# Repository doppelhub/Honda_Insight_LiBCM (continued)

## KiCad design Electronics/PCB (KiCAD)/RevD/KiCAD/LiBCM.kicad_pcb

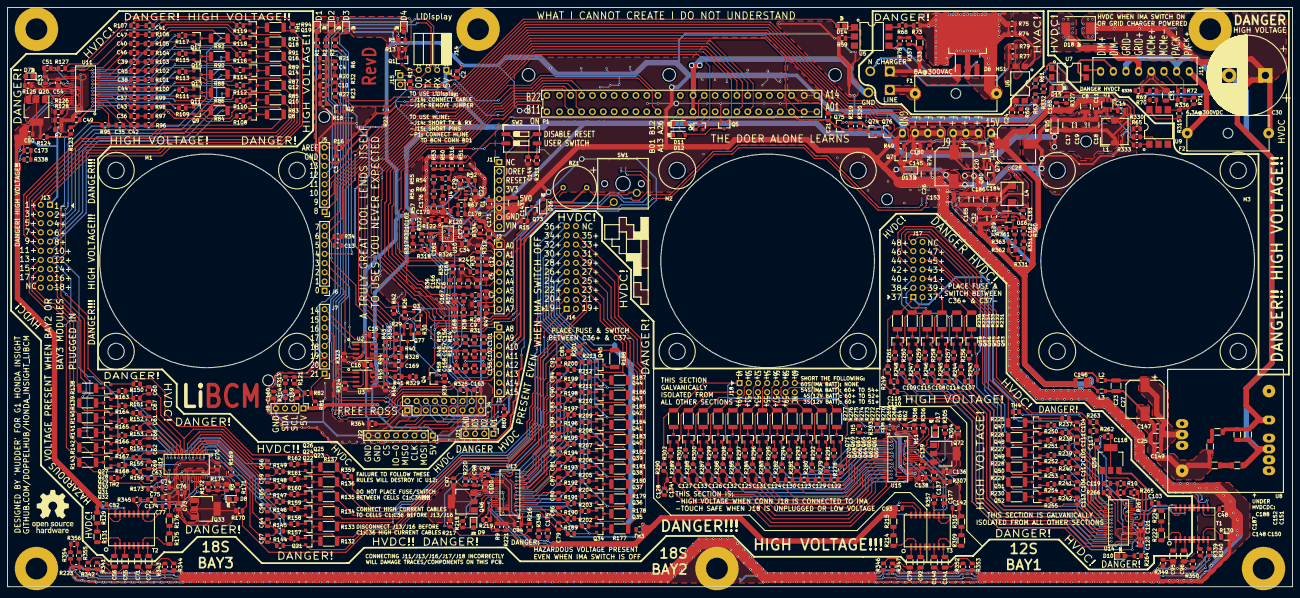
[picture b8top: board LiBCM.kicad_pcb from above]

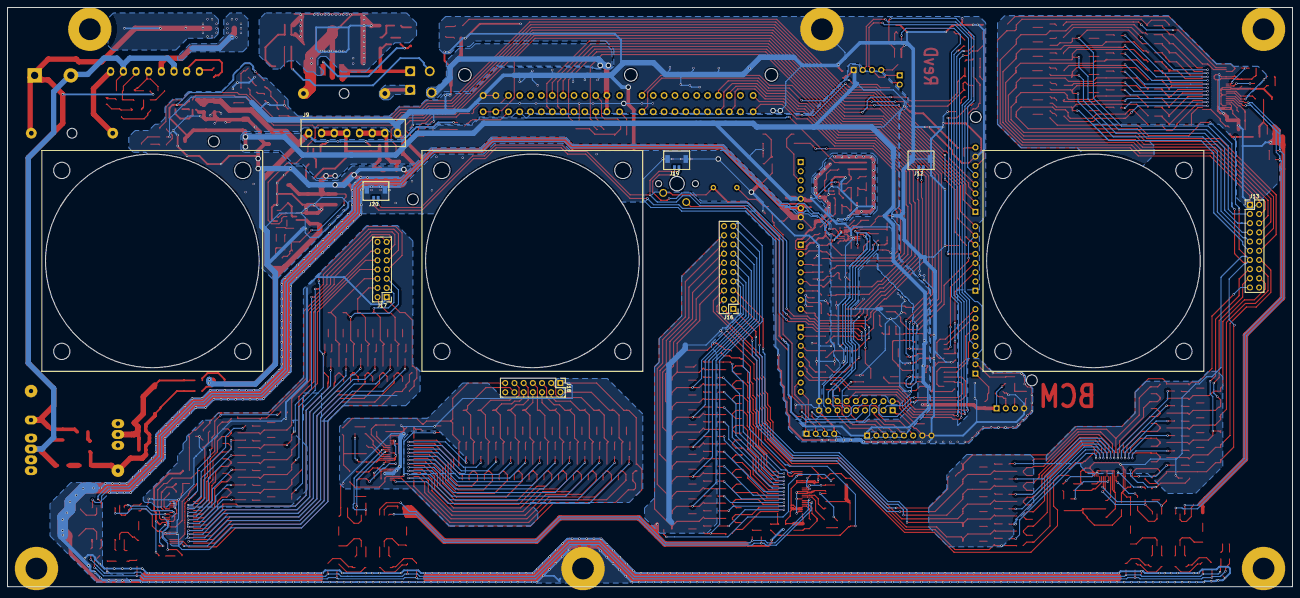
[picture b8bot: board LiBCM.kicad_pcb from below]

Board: 4 copper layers, 355.0 x 160.0 mm, 716 parts (8 on the bottom side), 583 nets.

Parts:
BZ1: Buzzer; BUZZER_WT-1205
C1, C2, C5, C6, C7, C9, C12, C13, C21, C24, C51, C53, C54, C74, C75, C76, C98, C99, C100, C101, C102, C119, C120, C121, C137, C138, C139, C144, C145, C147, C155, C156, C157, C158, C164, C166, C167, C168, C179, C180: 1u; C_0805_2012Metric
C3, C4, C10, C15, C16, C22, C29, C34, C35, C36, C37, C38, C39, C40, C41, C42, C43, C44, C45, C46, C47, C49, C50, C57, C58, C59, C60, C61, C62, C63, C64, C65, C66, C67, C68, C69, C70, C73, C79, C80, C81, C82, C83, C84, C85, C86, C87, C88, C89, C90, C91, C94, C97, C104, C105, C106, C107, C108, C109, C110, C111, C112, C113, C114, C115, C116, C117, C118, C122, C123, C124, C125, C126, C127, C128, C129, C130, C131, C132, C133, C134, C135, C136, C149, C165, C169, C176, C178, C181, C182: 100n; C_0805_2012Metric
C8, C18, C19, C143: DNP; C_1210_3225Metric
C11, C14, C170, C173, C174, C175, C177: DNP; C_0805_2012Metric
C17, C23, C25, C26, C32, C146, C153, C184, C185, C186: 22u; C_1210_3225Metric
C20, C27, C28: 220u; CP_Elec_10x10
C30: 33u; CP_Radial_D22.0mm_P10.00mm_SnapIn
C31, C151: 68n; C_1206_3216Metric
C33, C55, C56, C71, C72, C78, C92, C95, C96, C140, C141, C148, C150, C152, C187, C188: 22n; C_1206_3216Metric
C48, C52, C77, C93, C103, C142, C159, C160, C161, C162, C163, C171, C172: 100p; C_0805_2012Metric
D1, D2, D3, D4, D7, D8, D9, D10, D14, D15, D17: LED; LED_0805_2012Metric_Castellated
D5: D_Zener_ALT; D_SOD-123
D6: Q_TRIAC_A1A2G; TO-263-3_TabPin2
D11, D12, D13, D16: 1N4148W; D_SOD-123
D18: D; D_SMC
F1, F2: Fuse; Fuseholder_Cylinder-5x20mm_Schurter_0031_8201_Horizontal_Op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
H1, H2, H4, H5, H6, H7: MountingHole_Pad; MountingHole_6mm_Pad
H9: MountingHole; MountingHole_3mm
HS1: Heatsink_Pad; Heatsin-DV-T263-301E-TR
J1, J2, J3, J5, J6, J7: Conn_01x08; PinHeader_1x08_P2.54mm_Vertical
J4: Conn_02x09_Odd_Even; PinHeader_2x09_P2.54mm_Vertical
J8, J21: Conn_01x04; PinHeader_1x04_P2.54mm_Vertical
J9, J11: Screw_Terminal_01x08; CONN_1751303
J10: Screw_Terminal_01x01; SolderWire-1sqmm_1x01_D1.4mm_OD2.7mm
J12, J19, J20: Conn_02x02; CONN_WM26831CT-ND​
J13, J16: Conn_01x20; PinHeader_2x10_P2.54mm_Vertical
J14: Conn_01x04; PinSocket_1x04_P2.54mm_Horizontal
J15: Conn_01x02; PinHeader_1x02_P2.54mm_Vertical
J17, J18: Conn_01x14; PinHeader_2x07_P2.54mm_Vertical
J22: Conn_01x08; PinSocket_1x08_P2.54mm_Vertical
L1: DNP(4.7u); L_TDK_SLF7045
L2, L3: 1u; L_0805_2012Metric
L4: 15u; Inductor_CLF6045NI
M1, M2, M3: Fan; FAN_60x60OD_50x50Holes
P1: OEM_BCM_Connector; CONN_BCM_174917-6
P2: Conn_WallPlug_Earth; SolderWire-1sqmm_1x03_P5.4mm_D1.4mm_OD2.7mm
Q1, Q2, Q3, Q4, Q5, Q6, Q7, Q73, Q74, Q76, Q78, Q79, Q80: Q_NMOS_GSD; SOT-23
Q8, Q9, Q10, Q11, Q12, Q13, Q14, Q15, Q16, Q17, Q18, Q19, Q21, Q22, Q23, Q24, Q25, Q26, Q27, Q28, Q29, Q30, Q31, Q32, Q34, Q35, Q36, Q37, Q38, Q39, Q40, Q41, Q42, Q43, Q44, Q45, Q47, Q48, Q49, Q50, Q51, Q52, Q53, Q54, Q55, Q56, Q57, Q58, Q60, Q61, Q62, Q63, Q64, Q65, Q66, Q67, Q68, Q69, Q70, Q71, Q75, Q77: Q_PMOS_GSD; SOT-23
Q20, Q33, Q46, Q59, Q72: Q_NPN_BCEC; SOT-223
R1, R2, R3, R4, R5, R12, R14, R24, R25, R28, R31, R43, R44, R45, R46, R60, R81, R108, R109, R110, R111, R112, R113, R114, R115, R116, R117, R118, R119, R121, R122, R128, R157, R158, R159, R160, R161, R162, R163, R164, R165, R166, R167, R168, R174, R202, R203, R204, R205, R206, R207, R208, R209, R210, R211, R212, R213, R221, R250, R251, R252, R253, R254, R255, R256, R257, R258, R259, R260, R261, R267, R291, R292, R293, R294, R295, R296, R297, R298, R299, R300, R301, R302, R308, R326, R351, R360: 1k24; R_0805_2012Metric
R6, R20, R21, R66, R80, R323, R324: 71k5; R_0805_2012Metric
R7, R8, R9, R10, R11, R40, R41, R328, R329, R338, R345, R348, R357, R358, R364: DNP; R_0805_2012Metric
R13, R18, R19, R34, R35, R36, R37, R38, R48, R49, R51, R52, R55, R56, R58, R61, R69, R70, R71, R72, R127, R173, R220, R266, R307, R312, R315, R320, R335, R336, R361, R363: 10k; R_0805_2012Metric
R15, R26, R39, R42, R47, R57, R125, R171, R218, R264, R305, R317, R318, R319: 7k32; R_0805_2012Metric
R16, R17, R23, R50, R54, R59, R63, R65, R68, R73, R78, R82, R95, R96, R97, R98, R99, R100, R101, R102, R103, R104, R105, R106, R107, R123, R124, R144, R145, R146, R147, R148, R149, R150, R151, R152, R153, R154, R155, R156, R169, R170, R189, R190, R191, R192, R193, R194, R195, R196, R197, R198, R199, R200, R201, R216, R217, R223, R237, R238, R239, R240, R241, R242, R243, R244, R245, R246, R247, R248, R249, R262, R263, R278, R279, R280, R281, R282, R283, R284, R285, R286, R287, R288, R289, R290, R303, R304, R311, R313, R321, R322, R325, R330, R332, R333, R337, R354, R355: 100; R_0805_2012Metric
R22, R27, R32, R67, R74, R75, R77, R79, R331, R362: 100k; R_0805_2012Metric
R29, R33, R53, R120, R126, R172, R219, R265, R306, R316: 768; R_0805_2012Metric
R30, R314, R327, R334, R339, R340, R341, R342, R343, R344, R346, R347, R349, R350, R352, R353, R356, R359: 20; R_0805_2012Metric
R62, R64, R83, R84, R85, R86, R87, R88, R89, R90, R91, R92, R93, R94, R132, R133, R134, R135, R136, R137, R138, R139, R140, R141, R142, R143, R177, R178, R179, R180, R181, R182, R183, R184, R185, R186, R187, R188, R225, R226, R227, R228, R229, R230, R231, R232, R233, R234, R235, R236, R268, R269, R270, R271, R272, R273, R274, R275, R276, R277: 75; R_2010_5025Metric
R76: DNP(0); R_0805_2012Metric
R129, R130, R131, R175, R176, R214, R215, R222, R224, R309, R310: 5M; R_1206_3216Metric
SW1: SW_Push; SW_Cherry_MX_1.00u_PCB
SW2: SW_DIP_x02; SW_DIP_SPSTx02_Slide_9.78x7.26mm_W8.61mm_P2.54mm
T1, T2, T3: Trans_7490100111; Trans_7490100111A
TH1, TH2, TH3, TH4, TH5: THERMISTOR; R_0805_2012Metric
U1: AP63205WU; TSOT-23-6
U2, U3: LT1487; SOIC-8_3.9x4.9mm_P1.27mm
U4: LT1797; TSOT-23-5
U5: MOC3023M; SMDIP-6_W9.53mm
U6, U7: SFH620A-2X007T; SMDIP-4_W9.53mm_Clearance8mm
U8: EPM1510SJ; DCDC-EPM1210SJ
U9: H11D1SR2VM; SMDIP-6_W9.53mm
U10: LTC6820; LTC6820_MSOP
U11, U12, U13, U14, U15: LTC6804-2
U16: AP62301; TSOT-23-6

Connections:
+5V: BZ1.1, C1.1, C2.1, C15.2, C16.2, C17.1, C18.1, C19.1, C29.1, C34.1, C143.1, C153.1, C184.1, C185.1, C186.1, D5.1, D16.1, J1.5, J8.1, J14.1, J22.1, L1.1, L4.1, Q77.2, R16.1, R19.1, R22.1, R29.1, R35.1, R36.1, R37.1, R38.1, R48.1, R50.1, R53.1, R54.2, R58.1, R61.1, R81.2, R121.2, R311.2, R316.1, R317.1, R318.1, R326.1, R331.1, R358.2, R362.1, R363.1, SW1.2, SW2.3, U1.1, U2.8, U3.8, U4.5, U10.6, U10.7, U10.8, U10.9, U10.12
+5VP: C169.1, Q77.3, R43.1, R45.1, R358.1
+15V: C8.1, C11.1, C28.1, C32.1, C146.1, C165.1, C179.1, J9.1, L2.2, Q75.2, Q78.1, Q78.2, R76.1, R319.1, U1.3, U16.3
/5VP_GATE: Q77.1, R29.2, R30.1
/5V_BOOST: C14.2, U1.6
/5V_BOOST_ALT: C181.2, U16.6
/5V_COMP: C182.2, R363.2
/5V_ENABLE: C10.2, R22.2, R23.1, R27.1, R32.1, R327.2, U1.2, U16.5
/5V_EN_FET: Q2.3, R23.2
/5V_EN_PULSE: C165.2, R327.1
/5V_FB_ALT: C182.1, R360.2, R361.1, U16.4
/5V_SW: C14.1, L1.2, U1.5
/5V_SW_ALT: C181.1, L4.2, U16.2
/12NEG_RAW: C23.2, C25.2, C27.2, C147.2, C148.2, C149.1, C187.2, L3.2, U8.7
/12POS_RAW: C23.1, C25.1, C27.1, C147.1, C149.2, L2.1, U8.5
/12V_ALWAYS: D11.1, D12.1, P1.A13
/12V_KEYON: P1.A01, P1.A02, R6.2, R32.2
/38(HW_VER1): J4.2, R364.2
/52k5_L1: R331.2, R351.1, R362.2
/52k5_L2: R351.2, R360.1
/+12V_FAN: C20.1, C26.1, C145.1, C180.1, D13.1, J9.2, J9.3, J9.4, Q80.3, R76.2
/AREF: C3.1, J5.8, R16.2
/BATTFANH: D12.2, P1.A24, Q5.3
/BATTFANH_EN: J3.1, Q5.1, R42.1
/BATTFANL: D11.2, P1.A11, Q6.3
/BATTFANL_EN: J2.8, Q6.1, R47.1
/BATTSCI1: P1.A20, R46.1, R329.2, U3.6
/BATTSCI2: P1.A07, R41.1, R45.2, U3.7
/BATTSCI_DE: J4.3, R324.1, U3.3
/BATTSCI_REn: J4.4, U3.2
/BATTSCI_RX: J7.5, U3.1
/BATTSCI_TX: J7.6, U3.4
/BATT_CURRENT_ADC: C171.1, J2.1, R334.2
/BATT_CURRENT_I2V: C22.1, R51.1, R52.2, U4.3
/BAT_T: R41.2, R329.1
/BUZ1: BZ1.2, D16.2, Q73.3
/BUZZER: J4.7, Q73.1, R15.1
/COVER_SWITCH: J4.6, R80.1, SW1.1
/FAN-: C145.2, C180.2, D13.2, J9.5, J9.6, J9.7, Q7.3
/FAN_PWM: J5.4, Q7.1, R49.1
/GPIO-0: J4.5, J22.5
/GPIO-1: J3.7, J21.1
/GPIO-2: J3.8, J21.2
/GPIO-3: J4.8, J21.3
/GRID_EN: D14.2, J5.3
/GRID_EN_LED_A: D14.1, U5.1
/GRID_EN_LED_C: R59.2, U5.2
/GRID_HVDC+: D18.2, J11.4
/GRID_PWM: D15.2, J5.1
/GRID_PWM+: J11.1, U7.4
/GRID_PWM-: J11.2, U7.3
/GRID_PWM_DIV: R63.1, R332.1
/GRID_PWM_LED_A: D15.1, U7.1
/GRID_PWM_LED_C: R332.2, U7.2
/GRID_SENSE: C24.1, J5.2, R60.2
/GRID_SENSE_L1: R74.2, R75.2, U6.1
/GRID_SENSE_L2: R77.2, R79.2, U6.2
/GRID_SENSE_NOISY: R60.1, R61.2, U6.4
/HLINE: J15.2, R17.2
/HLINE_CONN: P1.B01, R17.1
/HMI_EN: J5.5, Q1.1, R13.1
/HMI_EN_OD: J14.4, Q1.3
/HMI_RX: J7.3, J14.2
/HMI_TX: J7.4, J14.3, J15.1
/HVDC_POS_UNFUSED: F2.1, J11.8
/IGNITION_SENSE: C4.1, J5.6, R20.1, R21.2
/I_SENSOR_NEG: C21.2, P1.A16, Q76.3
/I_SENSOR_POS: C21.1, P1.A03, Q75.3
/I_SENSOR_RAW: P1.A04, R50.2, R51.2, R53.2, R316.2
/KEYON_DIV: R6.1, R21.1
/L1: D6.2, F1.1, HS1.1, R73.1, R74.1, R75.1
/L1_GRID: C33.1, D6.1, J10.1, R337.1
/L1_SNUB: R78.1, R337.2
/L1_UNFUSED: F1.2, P2.1
/L2: P2.2, R77.1, R79.1
/LED1: J3.5, R1.2
/LED1R: D1.2, R1.1
/LED2: J3.6, R2.2
/LED2R: D2.2, R2.1
/LED3: J4.10, R3.2
/LED3R: D3.2, R3.1
/LED4: J4.12, R5.2
/LED4R: D4.2, R5.1
/LOAD5V_FET: Q3.3, R30.2
/LiBCM BMS/BIAS_A: R129.1, R131.2
/LiBCM BMS/BIAS_B: R175.2, R176.1
/LiBCM BMS/BIAS_C: R214.2, R215.1
/LiBCM BMS/BIAS_D: R222.2, R224.1
/LiBCM BMS/BIAS_E: R309.2, R310.1
/LiBCM BMS/C0_A: C41.2, C47.2, R107.1, U11.26
/LiBCM BMS/C0_B: C63.2, C69.2, R156.1, U12.26
/LiBCM BMS/C0_C: C85.2, C91.2, R201.1, U13.26
/LiBCM BMS/C0_D: C110.2, C116.2, R249.1, U14.26
/LiBCM BMS/C0_E: C128.2, C134.2, R290.1, U15.26
/LiBCM BMS/C1_A: C40.2, C47.1, R106.1, U11.24
/LiBCM BMS/C1_B: C62.2, C69.1, R155.1, U12.24
/LiBCM BMS/C1_C: C84.2, C91.1, R200.1, U13.24
/LiBCM BMS/C1_D: C109.2, C116.1, R248.1, U14.24
/LiBCM BMS/C1_E: C127.2, C134.1, R289.1, U15.24
/LiBCM BMS/C2_A: C40.1, C46.2, R105.1, U11.22
/LiBCM BMS/C2_B: C62.1, C68.2, R154.1, U12.22
/LiBCM BMS/C2_C: C84.1, C90.2, R199.1, U13.22
/LiBCM BMS/C2_D: C109.1, C115.2, R247.1, U14.22
/LiBCM BMS/C2_E: C127.1, C133.2, R288.1, U15.22
/LiBCM BMS/C3_A: C39.2, C46.1, R104.1, U11.20
/LiBCM BMS/C3_B: C61.2, C68.1, R153.1, U12.20
/LiBCM BMS/C3_C: C83.2, C90.1, R198.1, U13.20
/LiBCM BMS/C3_D: C108.2, C115.1, R246.1, U14.20
/LiBCM BMS/C3_E: C126.2, C133.1, R287.1, U15.20
/LiBCM BMS/C4_A: C39.1, C45.2, R103.1, U11.18
/LiBCM BMS/C4_B: C61.1, C67.2, R152.1, U12.18
/LiBCM BMS/C4_C: C83.1, C89.2, R197.1, U13.18
/LiBCM BMS/C4_D: C108.1, C114.2, R245.1, U14.18
/LiBCM BMS/C4_E: C126.1, C132.2, R286.1, U15.18
/LiBCM BMS/C5_A: C38.2, C45.1, R102.1, U11.16
/LiBCM BMS/C5_B: C60.2, C67.1, R151.1, U12.16
/LiBCM BMS/C5_C: C82.2, C89.1, R196.1, U13.16
/LiBCM BMS/C5_D: C107.2, C114.1, R244.1, U14.16
/LiBCM BMS/C5_E: C125.2, C132.1, R285.1, U15.16
/LiBCM BMS/C6_A: C38.1, C44.2, R101.1, U11.14
/LiBCM BMS/C6_B: C60.1, C66.2, R150.1, U12.14
/LiBCM BMS/C6_C: C82.1, C88.2, R195.1, U13.14
/LiBCM BMS/C6_D: C107.1, C113.2, R243.1, U14.14
/LiBCM BMS/C6_E: C125.1, C131.2, R284.1, U15.14
/LiBCM BMS/C7_A: C37.2, C44.1, R100.1, U11.12
/LiBCM BMS/C7_B: C59.2, C66.1, R149.1, U12.12
/LiBCM BMS/C7_C: C81.2, C88.1, R194.1, U13.12
/LiBCM BMS/C7_D: C106.2, C113.1, R242.1, U14.12
/LiBCM BMS/C7_E: C124.2, C131.1, R283.1, U15.12
/LiBCM BMS/C8_A: C37.1, C43.2, R99.1, U11.10
/LiBCM BMS/C8_B: C59.1, C65.2, R148.1, U12.10
/LiBCM BMS/C8_C: C81.1, C87.2, R193.1, U13.10
/LiBCM BMS/C8_D: C106.1, C112.2, R241.1, U14.10
/LiBCM BMS/C8_E: C124.1, C130.2, R282.1, U15.10
/LiBCM BMS/C9_A: C36.2, C43.1, R98.1, U11.8
/LiBCM BMS/C9_B: C58.2, C65.1, R147.1, U12.8
/LiBCM BMS/C9_C: C80.2, C87.1, R192.1, U13.8
/LiBCM BMS/C9_D: C105.2, C112.1, R240.1, U14.8
/LiBCM BMS/C9_E: C123.2, C130.1, R281.1, U15.8
/LiBCM BMS/C10_A: C36.1, C42.2, R97.1, U11.6
/LiBCM BMS/C10_B: C58.1, C64.2, R146.1, U12.6
/LiBCM BMS/C10_C: C80.1, C86.2, R191.1, U13.6
/LiBCM BMS/C10_D: C105.1, C111.2, R239.1, U14.6
/LiBCM BMS/C10_E: C123.1, C129.2, R280.1, U15.6
/LiBCM BMS/C10pos: J13.11, Q10.2, R84.2, R97.2
/LiBCM BMS/C11_A: C35.2, C42.1, R96.1, U11.4
/LiBCM BMS/C11_B: C57.2, C64.1, R145.1, U12.4
/LiBCM BMS/C11_C: C79.2, C86.1, R190.1, U13.4
/LiBCM BMS/C11_D: C104.2, C111.1, R238.1, U14.4
/LiBCM BMS/C11_E: C122.2, C129.1, R279.1, U15.4
/LiBCM BMS/C11pos: J13.12, Q9.2, R83.2, R96.2
/LiBCM BMS/C12_A: C35.1, R95.1, U11.2
/LiBCM BMS/C12_B: C57.1, R144.1, U12.2
/LiBCM BMS/C12_C: C79.1, R189.1, U13.2
/LiBCM BMS/C12_D: C104.1, R237.1, U14.2
/LiBCM BMS/C12_E: C122.1, R278.1, U15.2
/LiBCM BMS/CELL1pos: J13.2, Q19.2, R93.2, R106.2
/LiBCM BMS/CELL2pos: J13.3, Q18.2, R92.2, R105.2
/LiBCM BMS/CELL3pos: J13.4, Q17.2, R91.2, R104.2
/LiBCM BMS/CELL4pos: J13.5, Q16.2, R90.2, R103.2
/LiBCM BMS/CELL5pos: J13.6, Q15.2, R89.2, R102.2
/LiBCM BMS/CELL6pos: J13.7, Q14.2, R88.2, R101.2
/LiBCM BMS/CELL7pos: J13.8, Q13.2, R87.2, R100.2
/LiBCM BMS/CELL8pos: J13.9, Q12.2, R86.2, R99.2
/LiBCM BMS/CELL9pos: J13.10, Q11.2, R85.2, R98.2
/LiBCM BMS/CELL13pos: J13.14, Q32.2, R142.2, R155.2
/LiBCM BMS/CELL14pos: J13.15, Q31.2, R141.2, R154.2
/LiBCM BMS/CELL15pos: J13.16, Q30.2, R140.2, R153.2
/LiBCM BMS/CELL16pos: J13.17, Q29.2, R139.2, R152.2
/LiBCM BMS/CELL17pos: J13.18, Q28.2, R138.2, R151.2
/LiBCM BMS/CELL18pos: J13.19, Q27.2, R137.2, R150.2, R359.2
/LiBCM BMS/CELL19neg: J16.1, R359.1
/LiBCM BMS/CELL19pos: J16.2, Q26.2, R136.2, R149.2
/LiBCM BMS/CELL20pos: J16.3, Q25.2, R135.2, R148.2
/LiBCM BMS/CELL21pos: J16.4, Q24.2, R134.2, R147.2
/LiBCM BMS/CELL22pos: J16.5, Q23.2, R133.2, R146.2
/LiBCM BMS/CELL23pos: J16.6, Q22.2, R132.2, R145.2
/LiBCM BMS/CELL25pos: J16.8, Q45.2, R187.2, R200.2
/LiBCM BMS/CELL26pos: J16.9, Q44.2, R186.2, R199.2
/LiBCM BMS/CELL27pos: J16.10, Q43.2, R185.2, R198.2
/LiBCM BMS/CELL28pos: J16.11, Q42.2, R184.2, R197.2
/LiBCM BMS/CELL29pos: J16.12, Q41.2, R183.2, R196.2
/LiBCM BMS/CELL30pos: J16.13, Q40.2, R182.2, R195.2
/LiBCM BMS/CELL31pos: J16.14, Q39.2, R181.2, R194.2
/LiBCM BMS/CELL32pos: J16.15, Q38.2, R180.2, R193.2
/LiBCM BMS/CELL33pos: J16.16, Q37.2, R179.2, R192.2
/LiBCM BMS/CELL34pos: J16.17, Q36.2, R178.2, R191.2
/LiBCM BMS/CELL35pos: J16.18, Q35.2, R177.2, R190.2
/LiBCM BMS/CELL36pos: J16.19, Q34.2, R189.2, R216.1, R217.2
/LiBCM BMS/CELL37pos: J17.2, Q58.2, R235.2, R248.2
/LiBCM BMS/CELL38pos: J17.3, Q57.2, R234.2, R247.2
/LiBCM BMS/CELL39pos: J17.4, Q56.2, R233.2, R246.2
/LiBCM BMS/CELL40pos: J17.5, Q55.2, R232.2, R245.2
/LiBCM BMS/CELL41pos: J17.6, Q54.2, R231.2, R244.2
/LiBCM BMS/CELL42pos: J17.7, Q53.2, R230.2, R243.2
/LiBCM BMS/CELL43pos: J17.8, Q52.2, R229.2, R242.2
/LiBCM BMS/CELL44pos: J17.9, Q51.2, R228.2, R241.2
/LiBCM BMS/CELL45pos: J17.10, Q50.2, R227.2, R240.2
/LiBCM BMS/CELL46pos: J17.11, Q49.2, R226.2, R239.2
/LiBCM BMS/CELL47pos: J17.12, Q48.2, R225.2, R238.2
/LiBCM BMS/CELL48pos: J17.13, Q47.2, R237.2, R262.1, R263.2
/LiBCM BMS/CELL49pos: J18.2, Q71.2, R276.2, R289.2
/LiBCM BMS/CELL50pos: J18.3, Q70.2, R275.2, R288.2
/LiBCM BMS/CELL51pos: J18.4, Q69.2, R274.2, R287.2
/LiBCM BMS/CELL52pos: J18.5, Q68.2, R273.2, R286.2
/LiBCM BMS/CELL53pos: J18.6, Q67.2, R272.2, R285.2
/LiBCM BMS/CELL54pos: J18.7, Q66.2, R271.2, R284.2
/LiBCM BMS/CELL55pos: J18.8, Q65.2, R270.2, R283.2
/LiBCM BMS/CELL56pos: J18.9, Q64.2, R269.2, R282.2
/LiBCM BMS/CELL57pos: J18.10, Q63.2, R268.2, R281.2
/LiBCM BMS/CELL58pos: J18.11, Q62.2, R64.2, R280.2
/LiBCM BMS/CELL59pos: J18.12, Q61.2, R62.2, R279.2
/LiBCM BMS/CELL60pos: J18.13, Q60.2, R278.2, R303.1, R304.2
/LiBCM BMS/DRIVE_A: Q20.1, U11.38
/LiBCM BMS/DRIVE_B: Q33.1, U12.38
/LiBCM BMS/DRIVE_C: Q46.1, U13.38
/LiBCM BMS/DRIVE_D: Q59.1, U14.38
/LiBCM BMS/DRIVE_E: Q72.1, U15.38
/LiBCM BMS/IB_6820: R120.1, U10.16
/LiBCM BMS/IB_A: R126.1, U11.44
/LiBCM BMS/IB_B: R172.1, U12.44
/LiBCM BMS/IB_C: R219.1, U13.44
/LiBCM BMS/IB_D: R265.1, U14.44
/LiBCM BMS/IB_E: R306.1, U15.44
/LiBCM BMS/IC_6820: R120.2, R122.1, U10.15
/LiBCM BMS/IC_A: R7.2, R126.2, R128.2, U11.43
/LiBCM BMS/IC_B: R8.2, R172.2, R174.2, U12.43
/LiBCM BMS/IC_C: R9.2, R219.2, R221.2, U13.43
/LiBCM BMS/IC_D: R10.2, R265.2, R267.2, U14.43
/LiBCM BMS/IC_E: R11.2, R306.2, R308.2, U15.43
/LiBCM BMS/IMA_A: C173.1, T2.14, U11.41
/LiBCM BMS/IMA_B: C174.1, T2.9, U12.41
/LiBCM BMS/IMA_C: C175.1, T3.14, U13.41
/LiBCM BMS/IMA_D: T1.14, U14.41
/LiBCM BMS/IMA_E: C177.1, T3.9, U15.41
/LiBCM BMS/IM_6820: C172.1, T1.9, U10.10
/LiBCM BMS/IM_ISOA_X: C55.2, T2.3
/LiBCM BMS/IM_ISOB_X: C72.2, T2.8
/LiBCM BMS/IM_ISOC_X: C92.2, T3.3
/LiBCM BMS/IM_ISOD_X: C96.2, T1.3
/LiBCM BMS/IM_ISOE_X: C141.2, T3.8
/LiBCM BMS/IM_ISO_SAFETY: R340.2, T1.8
/LiBCM BMS/IM_ISO_STAR: R223.1, R340.1, R341.1, R344.1, R347.1, R350.1, R353.1, R355.1
/LiBCM BMS/IM_TERMA: C55.1, R341.2
/LiBCM BMS/IM_TERMB: C72.1, R344.2
/LiBCM BMS/IM_TERMC: C92.1, R347.2
/LiBCM BMS/IM_TERMD: C96.1, R350.2
/LiBCM BMS/IM_TERME: C141.1, R353.2
/LiBCM BMS/IM_TERM_STAR: R355.2, R356.1
/LiBCM BMS/IPA_A: R338.1, T2.16, U11.42
/LiBCM BMS/IPA_B: R345.1, T2.11, U12.42
/LiBCM BMS/IPA_C: R348.1, T3.16, U13.42
/LiBCM BMS/IPA_D: T1.16, U14.42
/LiBCM BMS/IPA_E: R357.1, T3.11, U15.42
/LiBCM BMS/IP_6820: C172.2, T1.11, U10.11
/LiBCM BMS/IP_ISOA_X: C56.2, T2.1
/LiBCM BMS/IP_ISOB_X: C71.2, T2.6
/LiBCM BMS/IP_ISOC_X: C78.2, T3.1
/LiBCM BMS/IP_ISOD_X: C95.2, T1.1
/LiBCM BMS/IP_ISOE_X: C140.2, T3.6
/LiBCM BMS/IP_ISO_SAFETY: R339.2, T1.6
/LiBCM BMS/IP_ISO_STAR: R223.2, R339.1, R342.1, R343.1, R346.1, R349.1, R352.1, R354.2
/LiBCM BMS/IP_TERMA: C56.1, R342.2
/LiBCM BMS/IP_TERMB: C71.1, R343.2
/LiBCM BMS/IP_TERMC: C78.1, R346.2
/LiBCM BMS/IP_TERMD: C95.1, R349.2
/LiBCM BMS/IP_TERME: C140.1, R352.2
/LiBCM BMS/IP_TERM_STAR: R354.1, R356.2
/LiBCM BMS/ISOA_TAP: R131.1, T2.2
/LiBCM BMS/ISOB_TAP: R175.1, T2.7
/LiBCM BMS/ISOC_TAP: R214.1, T3.2
/LiBCM BMS/ISOD_TAP: R222.1, T1.2
/LiBCM BMS/ISOE_TAP: R309.1, T3.7
/LiBCM BMS/LED_A: D7.2, R125.1
/LiBCM BMS/LED_B: D8.2, R171.1
/LiBCM BMS/LED_C: D9.2, R218.1
/LiBCM BMS/LED_D: D10.2, R264.1
/LiBCM BMS/LED_E: D17.2, R305.1
/LiBCM BMS/QC1_A: Q19.3, R94.1
/LiBCM BMS/QC1_B: Q32.3, R143.1
/LiBCM BMS/QC1_C: Q45.3, R188.1
/LiBCM BMS/QC1_D: Q58.3, R236.1
/LiBCM BMS/QC1_E: Q71.3, R277.1
/LiBCM BMS/QC2_A: Q18.3, R93.1
/LiBCM BMS/QC2_B: Q31.3, R142.1
/LiBCM BMS/QC2_C: Q44.3, R187.1
/LiBCM BMS/QC2_D: Q57.3, R235.1
/LiBCM BMS/QC2_E: Q70.3, R276.1
/LiBCM BMS/QC3_A: Q17.3, R92.1
/LiBCM BMS/QC3_B: Q30.3, R141.1
/LiBCM BMS/QC3_C: Q43.3, R186.1
/LiBCM BMS/QC3_D: Q56.3, R234.1
/LiBCM BMS/QC3_E: Q69.3, R275.1
/LiBCM BMS/QC4_A: Q16.3, R91.1
/LiBCM BMS/QC4_B: Q29.3, R140.1
/LiBCM BMS/QC4_C: Q42.3, R185.1
/LiBCM BMS/QC4_D: Q55.3, R233.1
/LiBCM BMS/QC4_E: Q68.3, R274.1
/LiBCM BMS/QC5_A: Q15.3, R90.1
/LiBCM BMS/QC5_B: Q28.3, R139.1
/LiBCM BMS/QC5_C: Q41.3, R184.1
/LiBCM BMS/QC5_D: Q54.3, R232.1
/LiBCM BMS/QC5_E: Q67.3, R273.1
/LiBCM BMS/QC6_A: Q14.3, R89.1
/LiBCM BMS/QC6_B: Q27.3, R138.1
/LiBCM BMS/QC6_C: Q40.3, R183.1
/LiBCM BMS/QC6_D: Q53.3, R231.1
/LiBCM BMS/QC6_E: Q66.3, R272.1
/LiBCM BMS/QC7_A: Q13.3, R88.1
/LiBCM BMS/QC7_B: Q26.3, R137.1
/LiBCM BMS/QC7_C: Q39.3, R182.1
/LiBCM BMS/QC7_D: Q52.3, R230.1
/LiBCM BMS/QC7_E: Q65.3, R271.1
/LiBCM BMS/QC8_A: Q12.3, R87.1
/LiBCM BMS/QC8_B: Q25.3, R136.1
/LiBCM BMS/QC8_C: Q38.3, R181.1
/LiBCM BMS/QC8_D: Q51.3, R229.1
/LiBCM BMS/QC8_E: Q64.3, R270.1
/LiBCM BMS/QC9_A: Q11.3, R86.1
/LiBCM BMS/QC9_B: Q24.3, R135.1
/LiBCM BMS/QC9_C: Q37.3, R180.1
/LiBCM BMS/QC9_D: Q50.3, R228.1
/LiBCM BMS/QC9_E: Q63.3, R269.1
/LiBCM BMS/QC10_A: Q10.3, R85.1
/LiBCM BMS/QC10_B: Q23.3, R134.1
/LiBCM BMS/QC10_C: Q36.3, R179.1
/LiBCM BMS/QC10_D: Q49.3, R227.1
/LiBCM BMS/QC10_E: Q62.3, R268.1
/LiBCM BMS/QC11_A: Q9.3, R84.1
/LiBCM BMS/QC11_B: Q22.3, R133.1
/LiBCM BMS/QC11_C: Q35.3, R178.1
/LiBCM BMS/QC11_D: Q48.3, R226.1
/LiBCM BMS/QC11_E: Q61.3, R64.1
/LiBCM BMS/QC12_A: Q8.3, R83.1
/LiBCM BMS/QC12_B: Q21.3, R132.1
/LiBCM BMS/QC12_C: Q34.3, R177.1
/LiBCM BMS/QC12_D: Q47.3, R225.1
/LiBCM BMS/QC12_E: Q60.3, R62.1
/LiBCM BMS/S1_A: R119.1, U11.25
/LiBCM BMS/S1_B: R168.1, U12.25
/LiBCM BMS/S1_C: R213.1, U13.25
/LiBCM BMS/S1_D: R261.1, U14.25
/LiBCM BMS/S1_E: R302.1, U15.25
/LiBCM BMS/S1b_A: Q19.1, R119.2
/LiBCM BMS/S1b_B: Q32.1, R168.2
/LiBCM BMS/S1b_C: Q45.1, R213.2
/LiBCM BMS/S1b_D: Q58.1, R261.2
/LiBCM BMS/S1b_E: Q71.1, R302.2
/LiBCM BMS/S2_A: R118.1, U11.23
/LiBCM BMS/S2_B: R167.1, U12.23
/LiBCM BMS/S2_C: R212.1, U13.23
/LiBCM BMS/S2_D: R260.1, U14.23
/LiBCM BMS/S2_E: R301.1, U15.23
/LiBCM BMS/S2b_A: Q18.1, R118.2
/LiBCM BMS/S2b_B: Q31.1, R167.2
/LiBCM BMS/S2b_C: Q44.1, R212.2
/LiBCM BMS/S2b_D: Q57.1, R260.2
/LiBCM BMS/S2b_E: Q70.1, R301.2
/LiBCM BMS/S3_A: R117.1, U11.21
/LiBCM BMS/S3_B: R166.1, U12.21
/LiBCM BMS/S3_C: R211.1, U13.21
/LiBCM BMS/S3_D: R259.1, U14.21
/LiBCM BMS/S3_E: R300.1, U15.21
/LiBCM BMS/S3b_A: Q17.1, R117.2
/LiBCM BMS/S3b_B: Q30.1, R166.2
/LiBCM BMS/S3b_C: Q43.1, R211.2
/LiBCM BMS/S3b_D: Q56.1, R259.2
/LiBCM BMS/S3b_E: Q69.1, R300.2
/LiBCM BMS/S4_A: R116.1, U11.19
/LiBCM BMS/S4_B: R165.1, U12.19
/LiBCM BMS/S4_C: R210.1, U13.19
/LiBCM BMS/S4_D: R258.1, U14.19
/LiBCM BMS/S4_E: R299.1, U15.19
/LiBCM BMS/S4b_A: Q16.1, R116.2
/LiBCM BMS/S4b_B: Q29.1, R165.2
/LiBCM BMS/S4b_C: Q42.1, R210.2
/LiBCM BMS/S4b_D: Q55.1, R258.2
/LiBCM BMS/S4b_E: Q68.1, R299.2
/LiBCM BMS/S5_A: R115.1, U11.17
/LiBCM BMS/S5_B: R164.1, U12.17
/LiBCM BMS/S5_C: R209.1, U13.17
/LiBCM BMS/S5_D: R257.1, U14.17
/LiBCM BMS/S5_E: R298.1, U15.17
/LiBCM BMS/S5b_A: Q15.1, R115.2
/LiBCM BMS/S5b_B: Q28.1, R164.2
/LiBCM BMS/S5b_C: Q41.1, R209.2
/LiBCM BMS/S5b_D: Q54.1, R257.2
/LiBCM BMS/S5b_E: Q67.1, R298.2
/LiBCM BMS/S6_A: R114.1, U11.15
/LiBCM BMS/S6_B: R163.1, U12.15
/LiBCM BMS/S6_C: R208.1, U13.15
/LiBCM BMS/S6_D: R256.1, U14.15
/LiBCM BMS/S6_E: R297.1, U15.15
/LiBCM BMS/S6b_A: Q14.1, R114.2
/LiBCM BMS/S6b_B: Q27.1, R163.2
/LiBCM BMS/S6b_C: Q40.1, R208.2
/LiBCM BMS/S6b_D: Q53.1, R256.2
/LiBCM BMS/S6b_E: Q66.1, R297.2
/LiBCM BMS/S7_A: R113.1, U11.13
/LiBCM BMS/S7_B: R162.1, U12.13
/LiBCM BMS/S7_C: R207.1, U13.13
/LiBCM BMS/S7_D: R255.1, U14.13
/LiBCM BMS/S7_E: R296.1, U15.13
/LiBCM BMS/S7b_A: Q13.1, R113.2
/LiBCM BMS/S7b_B: Q26.1, R162.2
/LiBCM BMS/S7b_C: Q39.1, R207.2
/LiBCM BMS/S7b_D: Q52.1, R255.2
/LiBCM BMS/S7b_E: Q65.1, R296.2
/LiBCM BMS/S8_A: R112.1, U11.11
/LiBCM BMS/S8_B: R161.1, U12.11
/LiBCM BMS/S8_C: R206.1, U13.11
/LiBCM BMS/S8_D: R254.1, U14.11
/LiBCM BMS/S8_E: R295.1, U15.11
/LiBCM BMS/S8b_A: Q12.1, R112.2
/LiBCM BMS/S8b_B: Q25.1, R161.2
/LiBCM BMS/S8b_C: Q38.1, R206.2
/LiBCM BMS/S8b_D: Q51.1, R254.2
/LiBCM BMS/S8b_E: Q64.1, R295.2
/LiBCM BMS/S9_A: R111.1, U11.9
/LiBCM BMS/S9_B: R160.1, U12.9
/LiBCM BMS/S9_C: R205.1, U13.9
/LiBCM BMS/S9_D: R253.1, U14.9
/LiBCM BMS/S9_E: R294.1, U15.9
/LiBCM BMS/S9b_A: Q11.1, R111.2
/LiBCM BMS/S9b_B: Q24.1, R160.2
/LiBCM BMS/S9b_C: Q37.1, R205.2
/LiBCM BMS/S9b_D: Q50.1, R253.2
/LiBCM BMS/S9b_E: Q63.1, R294.2
/LiBCM BMS/S10_A: R110.1, U11.7
/LiBCM BMS/S10_B: R159.1, U12.7
/LiBCM BMS/S10_C: R204.1, U13.7
/LiBCM BMS/S10_D: R252.1, U14.7
/LiBCM BMS/S10_E: R293.1, U15.7
/LiBCM BMS/S10b_A: Q10.1, R110.2
/LiBCM BMS/S10b_B: Q23.1, R159.2
/LiBCM BMS/S10b_C: Q36.1, R204.2
/LiBCM BMS/S10b_D: Q49.1, R252.2
/LiBCM BMS/S10b_E: Q62.1, R293.2
/LiBCM BMS/S11_A: R109.1, U11.5
/LiBCM BMS/S11_B: R158.1, U12.5
/LiBCM BMS/S11_C: R203.1, U13.5
/LiBCM BMS/S11_D: R251.1, U14.5
/LiBCM BMS/S11_E: R292.1, U15.5
/LiBCM BMS/S11b_A: Q9.1, R109.2
/LiBCM BMS/S11b_B: Q22.1, R158.2
/LiBCM BMS/S11b_C: Q35.1, R203.2
/LiBCM BMS/S11b_D: Q48.1, R251.2
/LiBCM BMS/S11b_E: Q61.1, R292.2
/LiBCM BMS/S12_A: R108.1, U11.3
/LiBCM BMS/S12_B: R157.1, U12.3
/LiBCM BMS/S12_C: R202.1, U13.3
/LiBCM BMS/S12_D: R250.1, U14.3
/LiBCM BMS/S12_E: R291.1, U15.3
/LiBCM BMS/S12b_A: Q8.1, R108.2
/LiBCM BMS/S12b_B: Q21.1, R157.2
/LiBCM BMS/S12b_C: Q34.1, R202.2
/LiBCM BMS/S12b_D: Q47.1, R250.2
/LiBCM BMS/S12b_E: Q60.1, R291.2
/LiBCM BMS/SNUBA: C173.2, R338.2
/LiBCM BMS/SNUBB: C174.2, R345.2
/LiBCM BMS/SNUBC: C175.2, R348.2
/LiBCM BMS/SNUBE: C177.2, R357.2
/LiBCM BMS/TCENTER_6820: C48.1, T1.10
/LiBCM BMS/TCENTER_A: C52.1, T2.15
/LiBCM BMS/TCENTER_B: C77.1, T2.10
/LiBCM BMS/TCENTER_C: C93.1, T3.15
/LiBCM BMS/TCENTER_D: C103.1, T1.15
/LiBCM BMS/TCENTER_E: C142.1, T3.10
/LiBCM BMS/TCENTER_ISO_SAFETY: R130.2, T1.7
/LiBCM BMS/T_A: R127.2, TH1.1, U11.27
/LiBCM BMS/T_B: R173.2, TH2.1, U12.27
/LiBCM BMS/T_C: R220.2, TH3.1, U13.27
/LiBCM BMS/T_D: R266.2, TH4.1, U14.27
/LiBCM BMS/T_E: R307.2, TH5.1, U15.27
/LiBCM BMS/VREF1_A: C53.2, U11.35
/LiBCM BMS/VREF1_B: C75.2, U12.35
/LiBCM BMS/VREF1_C: C99.2, U13.35
/LiBCM BMS/VREF1_D: C120.2, U14.35
/LiBCM BMS/VREF1_E: C138.2, U15.35
/LiBCM BMS/VREF2_A: C51.2, R127.1, U11.34
/LiBCM BMS/VREF2_B: C74.2, R173.1, U12.34
/LiBCM BMS/VREF2_C: C98.2, R220.1, U13.34
/LiBCM BMS/VREF2_D: C119.2, R266.1, U14.34
/LiBCM BMS/VREF2_E: C137.2, R307.1, U15.34
/LiBCM BMS/VREG_A: C54.2, Q20.3, R125.2, U11.36, U11.37, U11.40, U11.46
/LiBCM BMS/VREG_B: C76.2, Q33.3, R171.2, U12.36, U12.37, U12.40, U12.45, U12.46
/LiBCM BMS/VREG_C: C100.2, Q46.3, R218.2, U13.36, U13.37, U13.40, U13.47
/LiBCM BMS/VREG_D: C121.2, Q59.3, R264.2, U14.36, U14.37, U14.40, U14.45, U14.47
/LiBCM BMS/VREG_E: C139.2, Q72.3, R305.2, U15.36, U15.37, U15.40, U15.46, U15.47
/LiBCM BMS/VdriveCollector_A: C50.1, Q20.2, Q20.4, R124.1
/LiBCM BMS/VdriveCollector_B: C73.1, Q33.2, Q33.4, R170.1
/LiBCM BMS/VdriveCollector_C: C97.1, Q46.2, Q46.4, R217.1
/LiBCM BMS/VdriveCollector_D: C118.1, Q59.2, Q59.4, R263.1
/LiBCM BMS/VdriveCollector_E: C136.1, Q72.2, Q72.4, R304.1
/LiBCM BMS/VpFILT_A: C49.1, R123.2, U11.1
/LiBCM BMS/VpFILT_B: C70.1, R169.2, U12.1
/LiBCM BMS/VpFILT_C: C94.1, R216.2, U13.1
/LiBCM BMS/VpFILT_D: C117.1, R262.2, U14.1
/LiBCM BMS/VpFILT_E: C135.1, R303.2, U15.1
/LiBCM BMS/WDT_A: D7.1, U11.39
/LiBCM BMS/WDT_B: D8.1, U12.39
/LiBCM BMS/WDT_C: D9.1, U13.39
/LiBCM BMS/WDT_D: D10.1, U14.39
/LiBCM BMS/WDT_E: D17.1, U15.39
/MCM_E_B: R315.2, U9.6
/MCM_E_C: R70.1, U9.5
/MCM_E_C2: R70.2, R335.1
/MCM_E_CONN+: C31.2, J11.5, R69.2, R335.2
/MCM_E_CONN-: C31.1, J11.6, R72.1, R336.1
/MCM_E_CONTROL: J6.8, R330.1
/MCM_E_DIV: R330.2, R333.1
/MCM_E_E: R71.2, R315.1, U9.4
/MCM_E_E2: R71.1, R336.2
/MCM_E_LED_A: R333.2, U9.1
/MCM_E_LED_C: R65.2, U9.2
/METSCI1: P1.A21, R44.1, R328.2, U2.6
/METSCI2: P1.A08, R40.1, R43.2, U2.7
/METSCI_DE: J6.3, R323.1, U2.3
/METSCI_REn: J6.4, U2.2
/METSCI_RX: J7.7, U2.1
/METSCI_TX: J7.8, U2.4
/MET_T: R40.2, R328.1
/NEG_SAFETY: C148.1, C150.2
/OP_GAIN: C176.2, R55.1, R56.2, R66.2
/OP_IN-: C170.1, C178.1, R66.1, R67.2, U4.4
/OP_OFFSET_H: R54.1, R55.2
/OP_OFFSET_L: R56.1, R57.2
/OP_OUT: C178.2, R67.1, R334.1, U4.1
/POS_SAFETY: C187.1, C188.2
/Q74D: Q74.3, R320.2
/Q75G: Q75.1, R319.2, R320.1
/RESETcap: C144.1, R311.1, SW2.4
/RESETn: J1.3, SW2.1
/SCL: J7.1, R81.1, R82.2
/SCLc: C159.1, J8.2, R82.1
/SDA: J7.2, R121.1, R313.2
/SDAc: J8.3, R314.2
/SDAd: C160.1, R313.1, R314.1
/SENSOR_EN: J6.7, Q3.1, Q74.1, Q76.1, R26.1
/SPI_CS_EXT: J4.9, J22.6
/SPI_CS_LTC: J4.15, U10.5
/SPI_MISO: C163.1, J4.14, J22.4, R325.2
/SPI_MISO_FILT: R325.1, R326.2, U10.3
/SPI_MOSI: J4.13, J22.2, R317.2, R321.1
/SPI_MOSI_FILT: C162.2, R321.2, U10.2
/SPI_SCK: J4.16, J22.3, R318.2, R322.1
/SPI_SCK_FILT: C161.2, R322.2, U10.4
/TBATT_BAY1: C156.2, J20.1, R14.1, R19.2
/TBATT_BAY1_LPF: C101.2, J3.2, R14.2
/TBATT_BAY2: C157.2, J19.1, R12.1, R48.2
/TBATT_BAY2_LPF: C102.2, J3.3, R12.2
/TBATT_BAY3: C158.2, J12.1, R4.1, R58.2
/TBATT_BAY3_LPF: C155.2, J3.4, R4.2
/TEMP_BLU: C168.2, P1.B19, R31.1, R38.2
/TEMP_BLU_LPF: C9.2, J2.7, R31.2
/TEMP_EN: J4.11, Q4.1, R39.1
/TEMP_GRN: C166.2, P1.B20, R25.1, R36.2
/TEMP_GRN_LPF: C6.2, J2.5, R25.2
/TEMP_NEG: J12.2, J19.2, J20.2, P1.B12, Q4.3
/TEMP_WHT: C167.2, P1.B08, R28.1, R37.2
/TEMP_WHT_LPF: C7.2, J2.6, R28.2
/TEMP_YEL: C164.2, P1.B09, R24.1, R35.2
/TEMP_YEL_LPF: C5.2, J2.4, R24.2
/TRIAC_DRIVE: R68.2, U5.6
/TRIAC_GATE: D6.3, R78.2, U5.4
/TRIAC_SNUBBER: C33.2, R68.1, R73.2
/TURN_OFF_5V: J6.5, Q2.1, R18.1
/USER_SW: J2.2, R312.1, SW2.2
/VDROP_13: Q79.3, Q80.1, Q80.2
/VDROP_14: Q78.3, Q79.1, Q79.2
/VPIN_IN: C12.1, J2.3, R33.2
/VPIN_IN_NOISY: P1.B11, R33.1
/VPIN_OUT_LPF: C13.1, P1.B22, R34.1
/VPIN_OUT_PWM: J6.6, R34.2
GND_CHASSIS: P1.A12, P1.A25, P2.3
GND_ENG: C1.2, C2.2, C3.2, C4.2, C5.1, C6.1, C7.1, C8.2, C9.1, C10.1, C11.2, C12.2, C13.2, C15.1, C16.1, C17.2, C18.2, C19.2, C20.2, C22.2, C24.2, C26.2, C28.2, C29.2, C32.2, C34.2, C48.2, C101.1, C102.1, C143.2, C144.2, C146.2, C153.2, C155.1, C156.1, C157.1, C158.1, C159.2, C160.2, C161.1, C162.1, C163.2, C164.1, C166.1, C167.1, C168.1, C169.2, C170.2, C171.2, C176.1, C179.2, C184.2, C185.2, C186.2, D1.1, D2.1, D3.1, D4.1, D5.2, H1.1, H5.1, J1.6, J1.7, J4.1, J4.17, J4.18, J5.7, J8.4, J9.8, J12.3, J12.4, J19.3, J19.4, J20.3, J20.4, J21.4, J22.7, J22.8, L3.1, P1.A14, P1.A15, Q1.2, Q2.2, Q3.2, Q4.2, Q5.2, Q6.2, Q7.2, Q73.2, Q74.2, Q76.2, R13.2, R15.2, R18.2, R20.2, R26.2, R27.2, R39.2, R42.2, R44.2, R46.2, R47.2, R49.2, R52.1, R57.1, R59.1, R63.2, R65.1, R80.2, R122.2, R130.1, R312.2, R323.2, R324.2, R361.2, R364.1, U1.4, U2.5, U3.5, U4.2, U6.3, U10.1, U10.13, U10.14, U16.1
GND_ISO_A: C41.1, C49.2, C50.2, C51.1, C52.2, C53.1, C54.1, J13.1, R7.1, R94.2, R107.2, R128.1, R129.2, TH1.2, U11.30, U11.31, U11.45, U11.47, U11.48
GND_ISO_B: C63.1, C70.2, C73.2, C74.1, C75.1, C76.1, C77.2, J13.13, Q8.2, R8.1, R95.2, R123.1, R124.2, R143.2, R156.2, R174.1, R176.2, TH2.2, U12.30, U12.31, U12.47, U12.48
GND_ISO_C: C85.1, C93.2, C94.2, C97.2, C98.1, C99.1, C100.1, J16.7, Q21.2, R9.1, R144.2, R169.1, R170.2, R188.2, R201.2, R215.2, R221.1, TH3.2, U13.30, U13.31, U13.45, U13.46, U13.48
GND_ISO_D: C103.2, C110.1, C117.2, C118.2, C119.1, C120.1, C121.1, J17.1, R10.1, R224.2, R236.2, R249.2, R267.1, TH4.2, U14.30, U14.31, U14.46, U14.48
GND_ISO_E: C128.1, C135.2, C136.2, C137.1, C138.1, C139.1, C142.2, J18.1, R11.1, R277.2, R290.2, R308.1, R310.2, TH5.2, U15.30, U15.31, U15.45, U15.48
HVDC_NEG: C30.2, C150.1, C151.1, C152.1, J11.3, J11.7, R72.2, U8.10
HVDC_POS_FUSED: C30.1, C151.2, C152.2, C188.1, D18.1, F2.2, R69.1, U8.12
